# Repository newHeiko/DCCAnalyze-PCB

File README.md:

# DCCAnalyze hardware

This repo contains the PCB files for a stand-alone DCC analyzer.

## DCCAnalyze firmware

The firmware can be found at [newHeiko/DCCInspector-EX](https://github.com/newHeiko/DCCInspector-EX) which is an extension of [DCC-EX/DCCInspector-EX](https://github.com/DCC-EX/DCCInspector-EX) by the following points (some tbd).

- [x] Add support for Arduino Nano Every
- [ ] Add support for keys
- [ ] Add support for LCD

## Building DCCAnalyze hardware

The PCB was created with kicad 8.0, the production files with the Fabrication Toolkit.

Most of the parts are from my box of spare and leftover parts, which is why I mixed different size SMD parts, some also rather unusual.

This is the full partlist:
| Parts | Value | Notes / Source |
| ----- | ----- | -------------- |
| A1    | Arduino Nano Every | [Reichelt](https://www.reichelt.de/arduino-nano-every-atmega4809-ohne-header-ard-nano-eve-p261300.html?&nbc=1) |
| C1, C2 | 1nF  | 0805  |
| C3, C4, C5 | 100nF | 1206 |
| C6    | 47µF  | Dia 6.3mm, min 25V |
| D1, D2, D3, D4, D5, D6, D7, D8 | BAT42 | MiniMELF |
| J1 | RJ12-connector | [Reichelt](https://www.reichelt.de/modular-einbaubuchse-6-6-schwarz-mebp-6-6s-p11370.html?&nbc=1) |
| R1, R3 | 1kOhm | 1206 |
| R2 | 470Ohm | 1206 |
| R5 | 47Ohm | 0805 |
| RV1 | 500 Ohm | Piher PT-6 [Reichelt](https://www.reichelt.de/einstellpotentiometer-liegend-500-ohm-6-mm-pt-6-l-500-p14989.html?&nbc=1) |
| RV2 | 10kOhm | Piher PT-6 [Reichelt](https://www.reichelt.de/einstellpotentiometer-liegend-10-kohm-6-mm-pt-6-l-10k-p14982.html?&nbc=1) |
| SW2, SW3, SW4 | Digitast DT6 | [Reichelt](https://www.reichelt.de/eingabetaster-schaltspannung-100v-rund-sw-dt-6-sw-p7241.html?&nbc=1) |
| U1, U2 | 6N137 | DIP8 |
| LCD | 24x2 | [Reichelt](https://www.reichelt.de/lcd-modul-2x24-h-5-6mm-bl-ws-m-bel--lcd-242a-bl-p53951.html?&nbc=1) |
| SW1 | DPST or DPDT | [Reichelt](https://www.reichelt.de/schiebeschalter-miniatur-loetanschluss-2x-um-sw-t-217-p19976.html?&nbc=1) |
| DCC | 2x SKS SEB 2610 F4,8 | 2x [Reichelt](https://www.reichelt.de/einbaubuchse-4-mm-faston-gelb-gesichert-seb-2610f-ge-p106132.html?&nbc=1) |
| PinHeader for A1 | 2x 1x16 | 2x [Reichelt](https://www.reichelt.de/stiftleisten-2-54-mm-1x16-gerade-mpe-087-1-016-p119887.html?&nbc=1) |
| Socket for A1    | 2x 1x16 | 2x [Reichelt](https://www.reichelt.de/buchsenleisten-2-54-mm-1x16-gerade-mpe-094-1-016-p119919.html?&nbc=1) |
| PinHeader for LCD | 2x8 | [Reichelt](https://www.reichelt.de/stiftleisten-2-54-mm-2x08-gerade-mpe-087-2-016-p119897.html?&nbc=1) |
| Socket for LCD    | 2x8 | [Reichelt](https://www.reichelt.de/buchsenleiste-2x8-pol-vergoldet-2-54-bkl-10120808-p235674.html?&nbc=1) |
| 3x LCD stand-offs | 3x M2.5 x 12mm | |
| LCD screws | 6x M2.5 x 6mm | |
| PCB screw | 1x Dia 2.9mm x 6.5mm | |
| Enclosure | | 2x [Reichelt](https://www.reichelt.de/kunststoff-halbschale-123-x-70-x-14-5-mm-sd-10-gr-halb-p149274.html?&nbc=1) |

The device can decode the DCC signal either from the loconet(r) plug and its Railsync signal or from the two 4mm sockets. The sockets included in the BOM above are shorter than the ones I used for my prototype - they should fit in the recess of the PCB.

Power can come from the USB connection (then the DCC inputs both are optically isolated from everything else) or from the DCC / Railsync signal (then the USB connection is not required and the device can be used stand-alone). Power draw from DCC / Railsync is about 25mA-30mA at 15V.

The switch SW1 switches the device power from USB to DCC/Railsync. It should fit vertically between the RJ12 socket and the LCD / 4mm plugs.

Note that for the switch, the polarity matters. In the image above, the lower yellow wire needs to connect to the lower blue wire and the upper yellow wire to the upper blue wire.

You may substitute a classic Arduino Nano for the Arduino Nano Every, but the integrated linear voltage regulator of the classic Arduino Nano will probably get very hot. Beware of DCC / Railsync input voltages above ~12V or so in that case.

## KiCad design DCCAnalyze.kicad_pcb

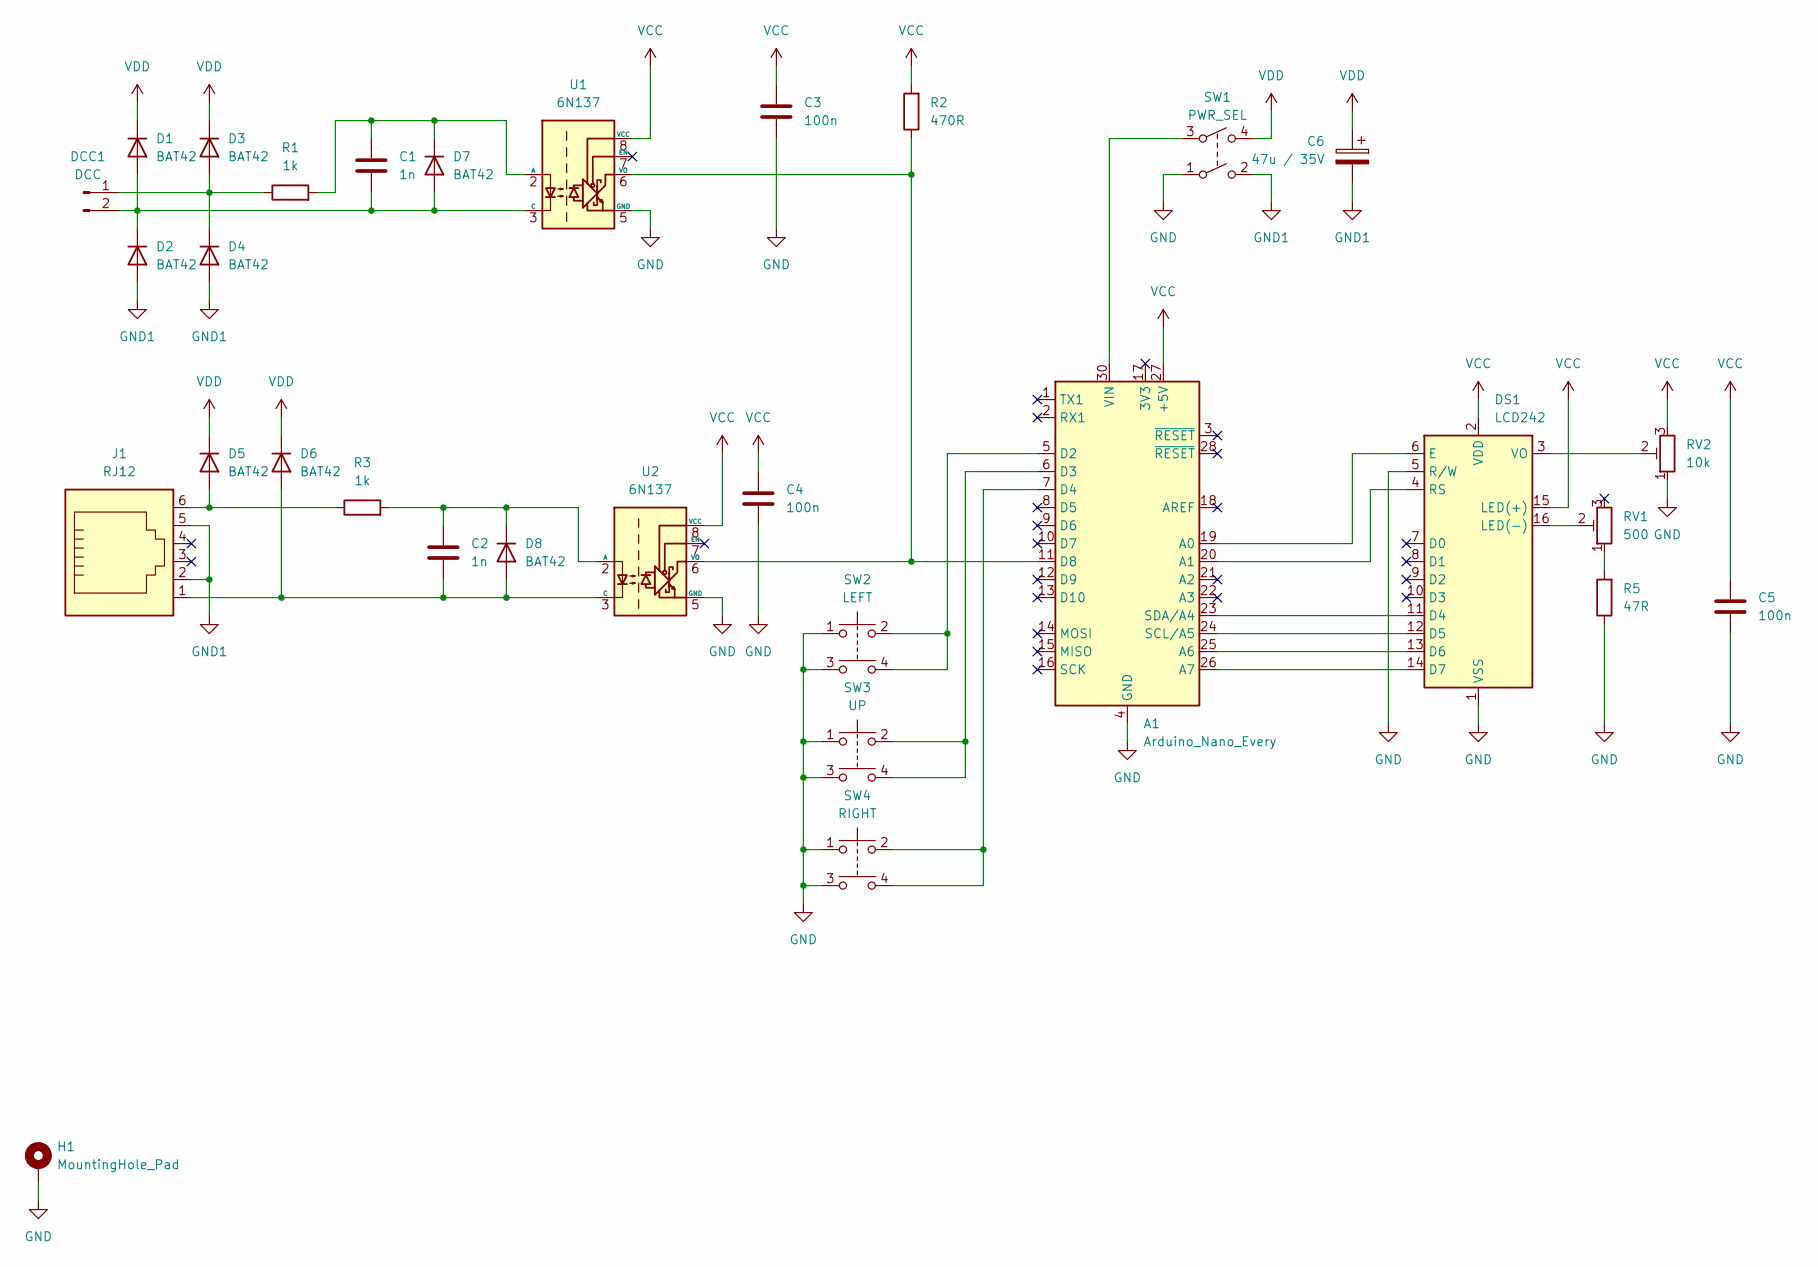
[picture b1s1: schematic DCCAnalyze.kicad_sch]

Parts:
A1: Arduino_Nano_Every; Arduino_Nano
C1, C2: 1n; C_0805_2012Metric_Pad1.18x1.45mm_HandSolder
C3, C4, C5: 100n; C_1206_3216Metric_Pad1.33x1.80mm_HandSolder
C6: 47u / 35V; CP_Elec_6.3x5.8
D1, D2, D3, D4, D5, D6, D7, D8: BAT42; D_MiniMELF_Handsoldering
DCC1: DCC; PinHeader_1x02_P2.54mm_Vertical
DS1: LCD242
H1: MountingHole_Pad; MountingHole_3.2mm_M3_Pad
J1: RJ12; RJ12_Amphenol_54601-x06_Horizontal
R1, R3: 1k; R_1206_3216Metric_Pad1.30x1.75mm_HandSolder
R2: 470R; R_1206_3216Metric_Pad1.30x1.75mm_HandSolder
R5: 47R; R_0805_2012Metric_Pad1.20x1.40mm_HandSolder
RV1: 500; Potentiometer_Piher_PT-6-V_Vertical
RV2: 10k; Potentiometer_Piher_PT-6-V_Vertical
SW1: PWR_SEL; PinHeader_2x02_P2.54mm_Vertical
SW2: LEFT; Push_E-Switch_KS01Q01
SW3: UP; Push_E-Switch_KS01Q01
SW4: RIGHT; Push_E-Switch_KS01Q01
U1, U2: 6N137; DIP-8_W7.62mm

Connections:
GND: A1.4 (GND), A1.29 (GND), C3.2, C4.2, C5.2, DS1.1 (VSS), DS1.5 (R/W), H1.1, R5.1, RV2.1, SW1.1, SW2.1, SW2.3, SW3.1, SW3.3, SW4.1, SW4.3, U1.5 (GND), U2.5 (GND)
GND1: C6.2, D2.2 (A), D4.2 (A), J1.2, J1.5, SW1.2
unnamed: A1.19 (A0), DS1.6 (E)
unnamed: A1.20 (A1), DS1.4 (RS)
unnamed: A1.25 (A6), DS1.13 (D6)
unnamed: A1.26 (A7), DS1.14 (D7)
unnamed: A1.5 (D2), SW2.2, SW2.4
unnamed: A1.6 (D3), SW3.2, SW3.4
unnamed: A1.7 (D4), SW4.2, SW4.4
unnamed: A1.11 (D8), R2.1, U1.6 (VO), U2.6 (VO)
unnamed: A1.24 (SCL/A5), DS1.12 (D5)
unnamed: A1.23 (SDA/A4), DS1.11 (D4)
unnamed: A1.30 (VIN), SW1.3
unnamed: C1.2, D1.2 (A), D2.1 (K), D7.2 (A), DCC1.2, U1.3 (C)
unnamed: D3.2 (A), D4.1 (K), DCC1.1, R1.1
unnamed: D5.2 (A), J1.6, R3.1
unnamed: C2.2, D6.2 (A), D8.2 (A), J1.1, U2.3 (C)
unnamed: C1.1, D7.1 (K), R1.2, U1.2 (A)
unnamed: C2.1, D8.1 (K), R3.2, U2.2 (A)
unnamed: DS1.16 (LED(-)), RV1.2
unnamed: DS1.3 (VO), RV2.2
unnamed: R5.2, RV1.1
VCC: A1.27 (+5V), C3.1, C4.1, C5.1, DS1.2 (VDD), DS1.15 (LED(+)), R2.2, RV2.3, U1.8 (VCC), U2.8 (VCC)
VDD: C6.1, D1.1 (K), D3.1 (K), D5.1 (K), D6.1 (K), SW1.4

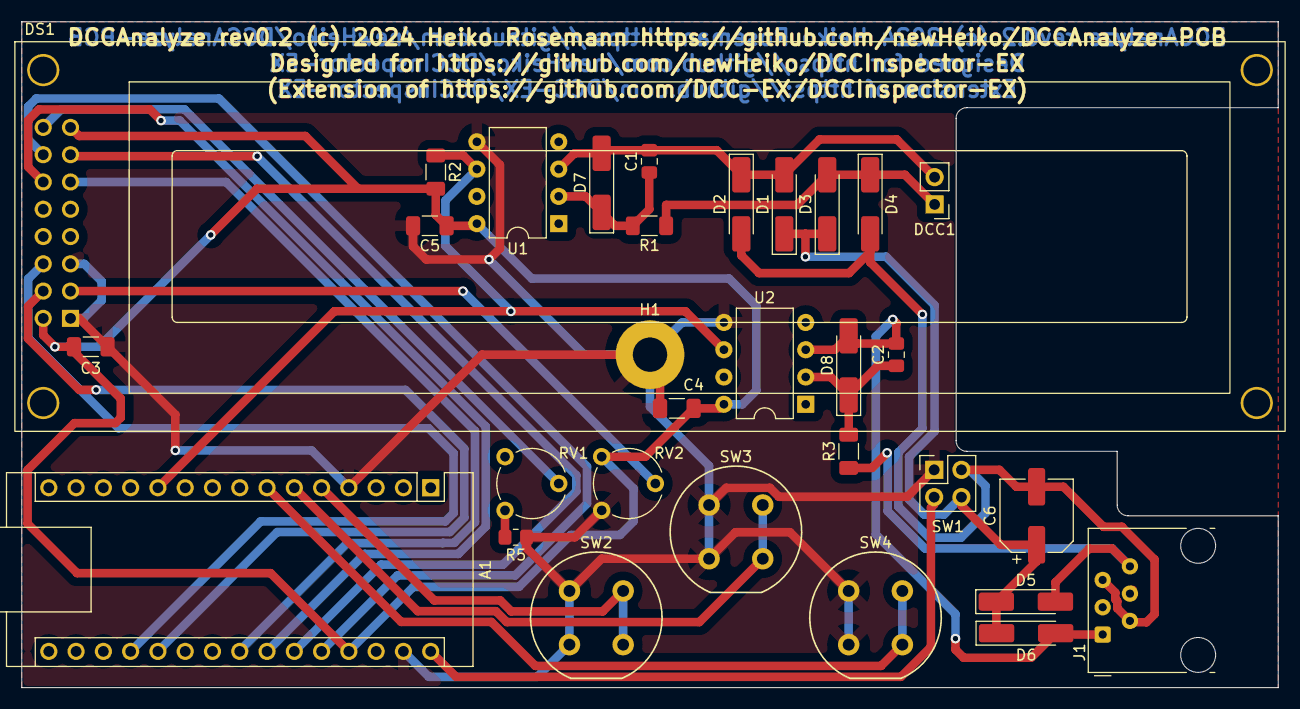
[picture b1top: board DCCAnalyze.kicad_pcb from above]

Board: 2 copper layers, 117.0 x 62.0 mm, 31 parts (0 on the bottom side), 24 nets.

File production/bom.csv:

Designator,Footprint,Quantity,Value,LCSC Part #
A1,Arduino_Nano,1,Arduino_Nano_Every,
"C1, C2",0805,2,1n,
"C3, C4, C5",1206,3,100n,
C6,CP_Elec_6.3x5.8,1,47u / 35V,
"D1, D2, D3, D4, D5, D6, D7, D8",D_MiniMELF_Handsoldering,8,BAT42,
DCC1,PinHeader_1x02_P2.54mm_Vertical,1,DCC,
DS1,LCD242,1,WC1602A,
J1,RJ12_Amphenol_54601-x06_Horizontal,1,RJ12,
"R1, R3",1206,2,1k,
R2,1206,1,470R,
R5,0805,1,47R,
RV1,Potentiometer_Piher_PT-6-V_Vertical,1,500,
RV2,Potentiometer_Piher_PT-6-V_Vertical,1,10k,
SW1,PinHeader_2x02_P2.54mm_Vertical,1,PWR_SEL,
SW2,Push_E-Switch_KS01Q01,1,LEFT,
SW3,Push_E-Switch_KS01Q01,1,UP,
SW4,Push_E-Switch_KS01Q01,1,RIGHT,
"U1, U2",DIP-8_W7.62mm,2,6N137,

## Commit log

2024-05-17 Add PCB v0.1 to github.
2024-05-17 Add gitignore for kicad backups
2024-05-17 Add some kicad interface file
2024-05-18 Move RJ12 connector inwards to match housing.
    ...for rev0.2
2024-05-19 Add a first attempt at documentation.
2024-05-19 Update README.md formatting
2024-05-19 Add position of power switch.
2024-05-19 Correct LCD value
2024-05-19 Update production data
2024-05-19 Add schematic images
2024-05-19 Add power consumption information.

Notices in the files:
DCCAnalyze.kicad_pcb:
DCCAnalyze rev0.2 (c) 2024 Heiko Rosemann https://github.com/newHeiko/DCCAnalyze-PCB
